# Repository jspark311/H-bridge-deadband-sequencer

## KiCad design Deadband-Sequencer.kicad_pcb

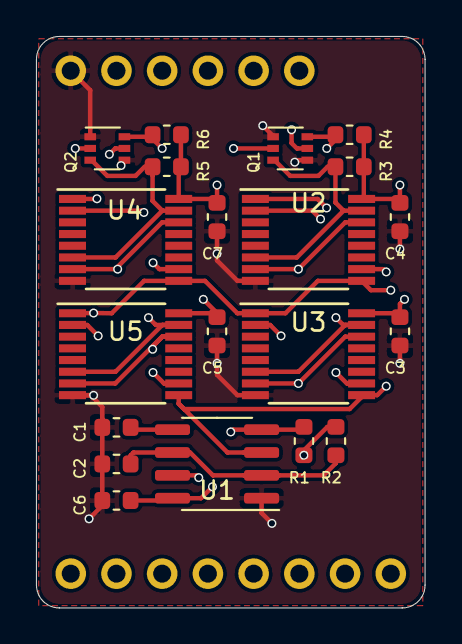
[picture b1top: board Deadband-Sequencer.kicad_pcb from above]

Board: 4 copper layers, 21.6 x 31.8 mm, 22 parts (0 on the bottom side), 22 nets.

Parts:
C1: 10nF; C_0603_1608Metric
C2, C3, C4, C5, C6, C7: 1uF; C_0603_1608Metric
J1: Conn_01x06; PinHeader_1x06_P2.54mm_Vertical
J2: Conn_01x08; PinHeader_1x08_P2.54mm_Vertical
Q1, Q2: MUN5232DW1T1GOSCT; SOT-363_SC-70-6
R1: 5k6; R_0603_1608Metric
R2: 15k; R_0603_1608Metric
R3, R4, R5, R6: 4k7; R_0603_1608Metric
U1: NE555D; SOIC-8_3.9x4.9mm_P1.27mm
U2, U3, U4, U5: 4015; TSSOP-16_4.4x5mm_P0.65mm

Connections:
/A_IN_1: J1.1, Q1.5, U2.7, U2.14
/A_IN_2: J1.2, Q1.2, U3.7, U3.14
/A_OUT_H1: J2.1, U2.10
/A_OUT_H2: J2.3, U3.10
/A_OUT_L1: J2.2, U2.2
/A_OUT_L2: J2.4, U3.2
/B_IN_1: J1.3, Q2.5, U4.7, U4.14
/B_IN_2: J1.4, Q2.2, U5.7, U5.14
/B_OUT_H1: J2.5, U4.10
/B_OUT_H2: J2.7, U5.10
/B_OUT_L1: J2.6, U4.2
/B_OUT_L2: J2.8, U5.2
/CLK: U1.3, U2.1, U2.9, U3.1, U3.9, U4.1, U4.9, U5.1, U5.9
/~A_IN_1: Q1.3, R3.2, U2.6, U2.15
/~A_IN_2: Q1.6, R4.2, U3.6, U3.15
/~B_IN_1: Q2.3, R5.2, U4.6, U4.15
/~B_IN_2: Q2.6, R6.2, U5.6, U5.15
GND: C1.2, C2.2, C3.1, C4.1, C5.1, C6.1, C7.1, J1.6, Q1.1, Q1.4, Q2.1, Q2.4, U1.1, U2.8, U3.8, U4.8, U5.8
unnamed: C1.1, U1.5
unnamed: C2.1, R2.1, U1.2, U1.6
unnamed: R1.1, R2.2, U1.7
VCC: C3.2, C4.2, C5.2, C6.2, C7.2, J1.5, R1.2, R3.1, R4.1, R5.1, R6.1, U1.4, U1.8, U2.16, U3.16, U4.16, U5.16

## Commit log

2022-02-23 Initial commit.
2022-03-02 Adding part datasheets.
